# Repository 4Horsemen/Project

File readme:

----------12/01/14 - 12/07/14 T17 Weekly Update 7-----------
*Thomas and Brian soldered all components onto their PCBs
*Thomas and Brian verified their PCBs had no solder bridges
*Fabricated bamboo parts for our Useless Box
*Worked on finalizing code for the Useless Box
*Designed arm mechanism for our Useless Box

----------11/24/14 - 11/30/14 T17 Weekly Update 6-----------
*Turned in HW#6
*Finished purchasing all components for PCB
*Thomas and Brian got cleared to work in the EPL & use
 the laser cutter, reflow oven, and soldering stations

----------11/17/14 - 11/23/14 T17 Weekly Update 5-----------
*Assembled our first board and baked it in the oven
*Started on HW#6
*Finalized the design for our test plan and test cases for HW#6

-----------11/10/14 - 11/16/14 T17 Weekly Update 4----------
Completed Tasks:
*Received our PCBs from Osh Park Manufacturing
*Began HW#5
*Researched HW#5
*Completed HW#5 Version #1
*Completed HW#5 Revision #2

-----------11/03/14 - 11/09/14 T17 Weekly Update 3-----------
Completed Tasks:
*Eliminated all unnecessary components in our PCB design
*Finalized our PCB design
*Submitted our PCB design inside the allotted time window
*Began HW#4
*Revised and expanded HW#4
*Completed HW#4
*Began to program Arduino and motor microcontrollers
*Ordered final parts

-----------10/27/14 - 11/02/14 T17 Weekly Update 2------------
Completed tasks:
*Got all of our ICs for our projects ordered
*Designed our schematic
*Fixed communication issues
*Finalized our black box
*Turned in HW#3 Rev#3
*Collective mentality shift.

-----------10/23/14 - 10/24/14 T17 Weekly Update 1------------
Completed tasks:
*Create a weekly update template
*Completed Rev1 HW 3
*Rough draft of Black box design completed

*Updated Block Diagram

To be done next week:
*Start ordering parts
*finish Atmega328 research
*finish LED Array research
*finish Servo research

Issues:
*Not sure what circuitry would be needed for LED arrays
*Not sure of motor/servo control circutry
*Getting Patrick, Ahmad, and Thomas on to git
*Getting the Atmega to respond to our preferences

---------------------------------------------------

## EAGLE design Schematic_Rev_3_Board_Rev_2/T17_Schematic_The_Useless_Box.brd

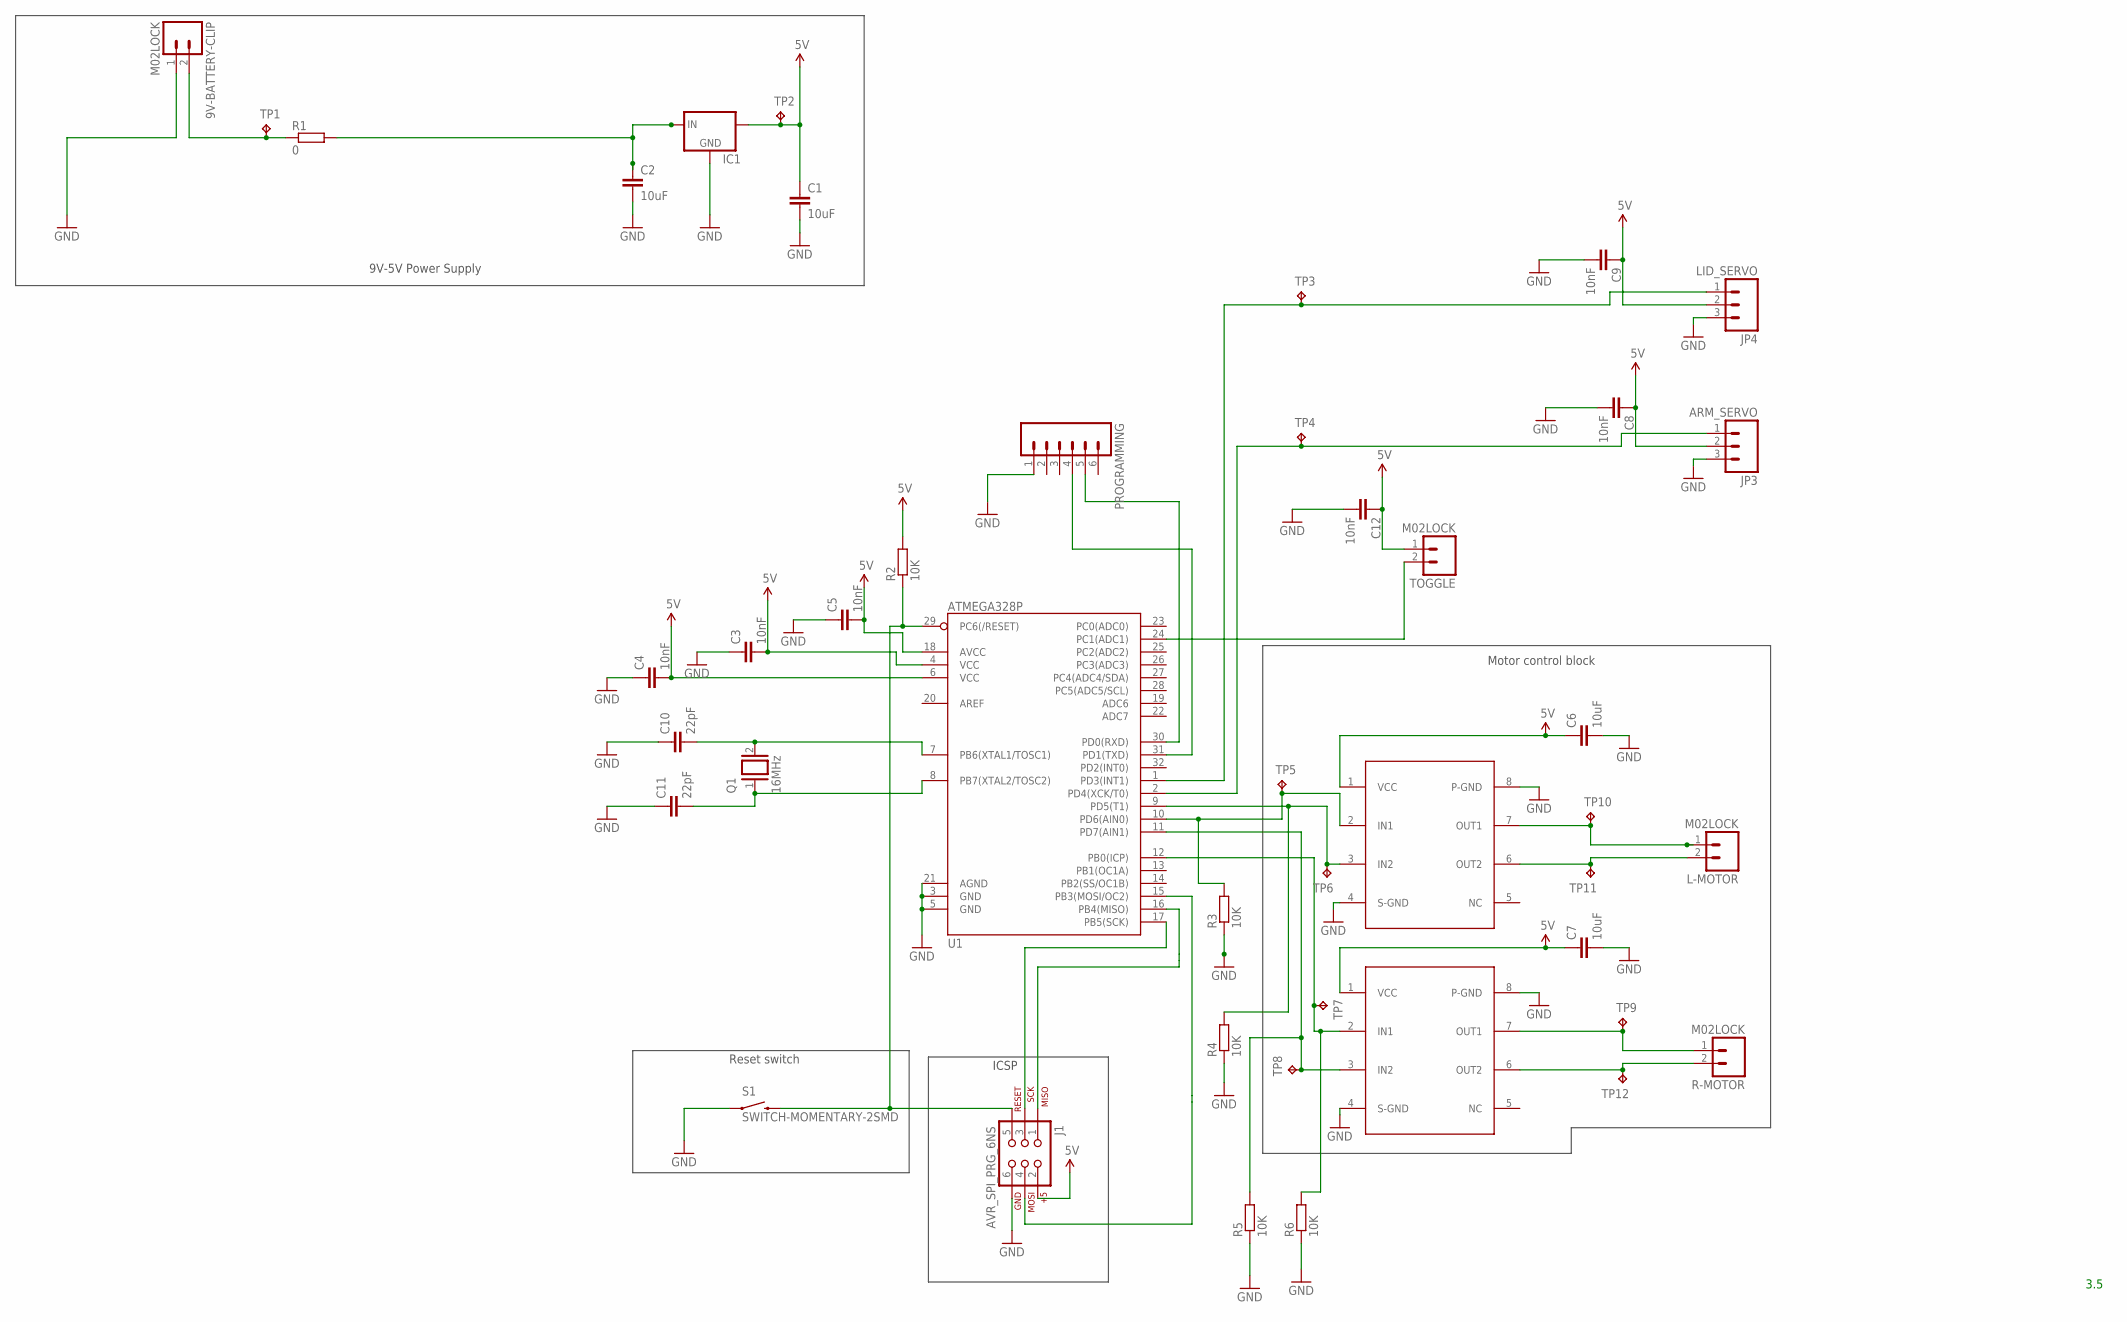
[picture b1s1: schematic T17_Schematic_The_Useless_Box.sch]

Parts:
9V-BATTERY-CLIP: M02LOCK; 1X02_LOCK
C1, C2, C6, C7: 10uF; C0805
C3, C4, C5, C8, C9, C12: 10nF; C0805
C10, C11: 22pF; C0805
IC1: V_REG_78XX-TO-220; TO-220-ALT
J1: AVR_SPI_PRG_6NS; 2X3-NS
JP3: ARM_SERVO; 1X03
JP4: LID_SERVO; 1X03
L-MOTOR: M02LOCK; 1X02_LOCK
PROGRAMMING: M06NO_SILK_FEMALE_PTH; 1X06_NO_SILK
Q1: 16MHz; QS
R1: 0; R0805
R2, R3, R4, R5, R6: 10K; R0805
R-MOTOR: M02LOCK; 1X02_LOCK
S1: SWITCH-MOMENTARY-2SMD; TACTILE-SWITCH-SMD
TOGGLE: M02LOCK; 1X02_LOCK
TP1, TP2, TP3, TP4, TP5, TP6, TP7, TP8, TP9, TP10, TP11, TP12: TPB1,27; B1,27
U1: ATMEGA328P; TQFP32-08
U$1, U$2: LB1938FA-AH; MSOP8

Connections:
5V: C1.1, C3.2, C4.2, C5.2, C6.1, C7.1, C8.1, C9.1, C12.1, IC1.OUT, J1.2, JP3.2, JP4.2, R2.2, TOGGLE.1, TP2.TP, U1.4 (VCC), U1.6 (VCC), U1.18 (AVCC), U$1.1 (VCC), U$2.1 (VCC)
GND: 9V-BATTERY-CLIP.1, C1.2, C2.2, C3.1, C4.1, C5.1, C6.2, C7.2, C8.2, C9.2, C10.1, C11.1, C12.2, IC1.GND, J1.6, JP3.3, JP4.3, PROGRAMMING.1, R3.1, R4.1, R5.1, R6.1, S1.1, U1.3 (GND), U1.5 (GND), U1.21 (AGND), U$1.4 (S-GND), U$1.8 (P-GND), U$2.4 (S-GND), U$2.8 (P-GND)
unnamed: R6.2, TP7.TP, U1.12 (PB0(ICP)), U$1.2 (IN1)
unnamed: R-MOTOR.1, TP9.TP, U$1.7 (OUT1)
unnamed: R-MOTOR.2, TP12.TP, U$1.6 (OUT2)
unnamed: L-MOTOR.2, TP11.TP, U$2.6 (OUT2)
unnamed: L-MOTOR.1, TP10.TP, U$2.7 (OUT1)
unnamed: R5.2, TP8.TP, U1.11 (PD7(AIN1)), U$1.3 (IN2)
unnamed: J1.4, U1.15 (PB3(MOSI/OC2))
unnamed: JP3.1, TP4.TP, U1.2 (PD4(XCK/T0))
unnamed: PROGRAMMING.5, U1.30 (PD0(RXD))
unnamed: JP4.1, TP3.TP, U1.1 (PD3(INT1))
unnamed: C2.1, IC1.IN, R1.2
unnamed: 9V-BATTERY-CLIP.2, R1.1, TP1.TP
unnamed: R3.2, TP5.TP, U1.10 (PD6(AIN0)), U$2.2 (IN1)
unnamed: J1.3, U1.17 (PB5(SCK))
unnamed: PROGRAMMING.4, U1.31 (PD1(TXD))
unnamed: J1.5, R2.1, S1.3 (2), U1.29 (PC6(/RESET))
unnamed: C11.2, Q1.1, U1.8 (PB7(XTAL2/TOSC2))
unnamed: J1.1, U1.16 (PB4(MISO))
unnamed: C10.2, Q1.2, U1.7 (PB6(XTAL1/TOSC1))
unnamed: R4.2, TP6.TP, U1.9 (PD5(T1)), U$2.3 (IN2)
unnamed: TOGGLE.2, U1.24 (PC1(ADC1))

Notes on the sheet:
3.5
Motor control block
ICSP
Reset switch
9V-5V Power Supply

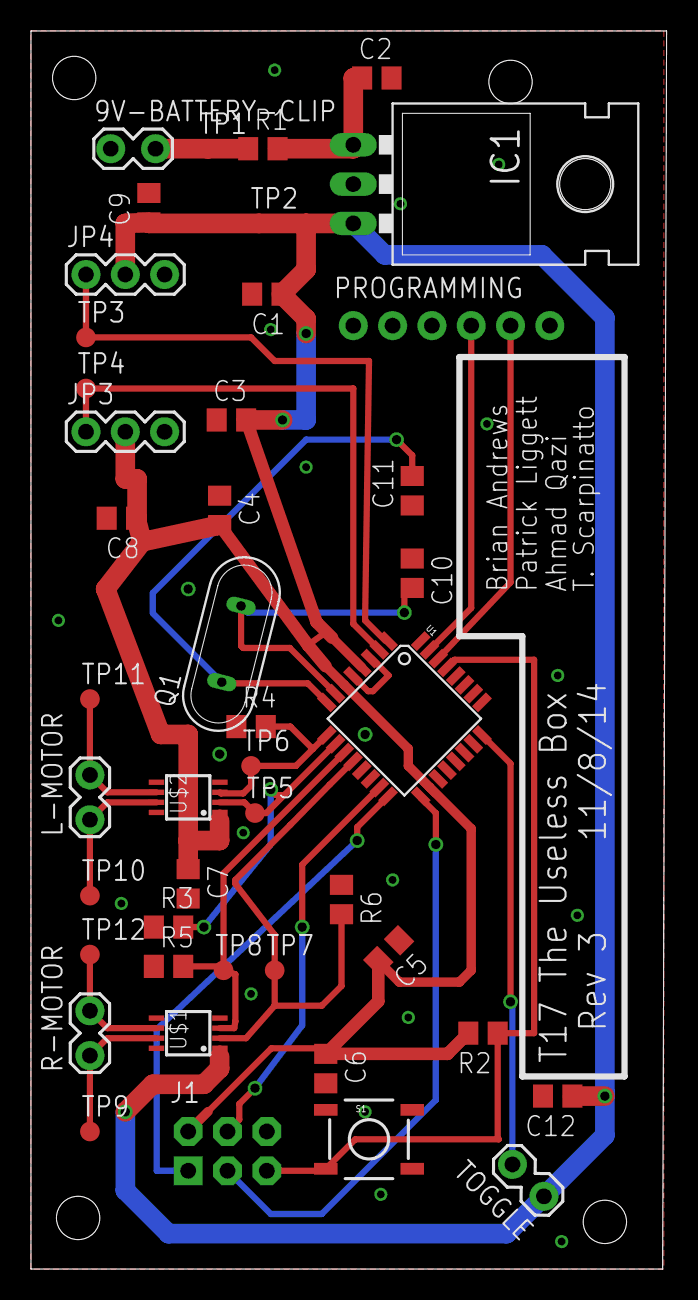
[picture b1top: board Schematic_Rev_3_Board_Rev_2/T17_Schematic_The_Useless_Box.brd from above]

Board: 2 copper layers, 41.1 x 80.0 mm, 44 parts (0 on the bottom side), 23 nets.

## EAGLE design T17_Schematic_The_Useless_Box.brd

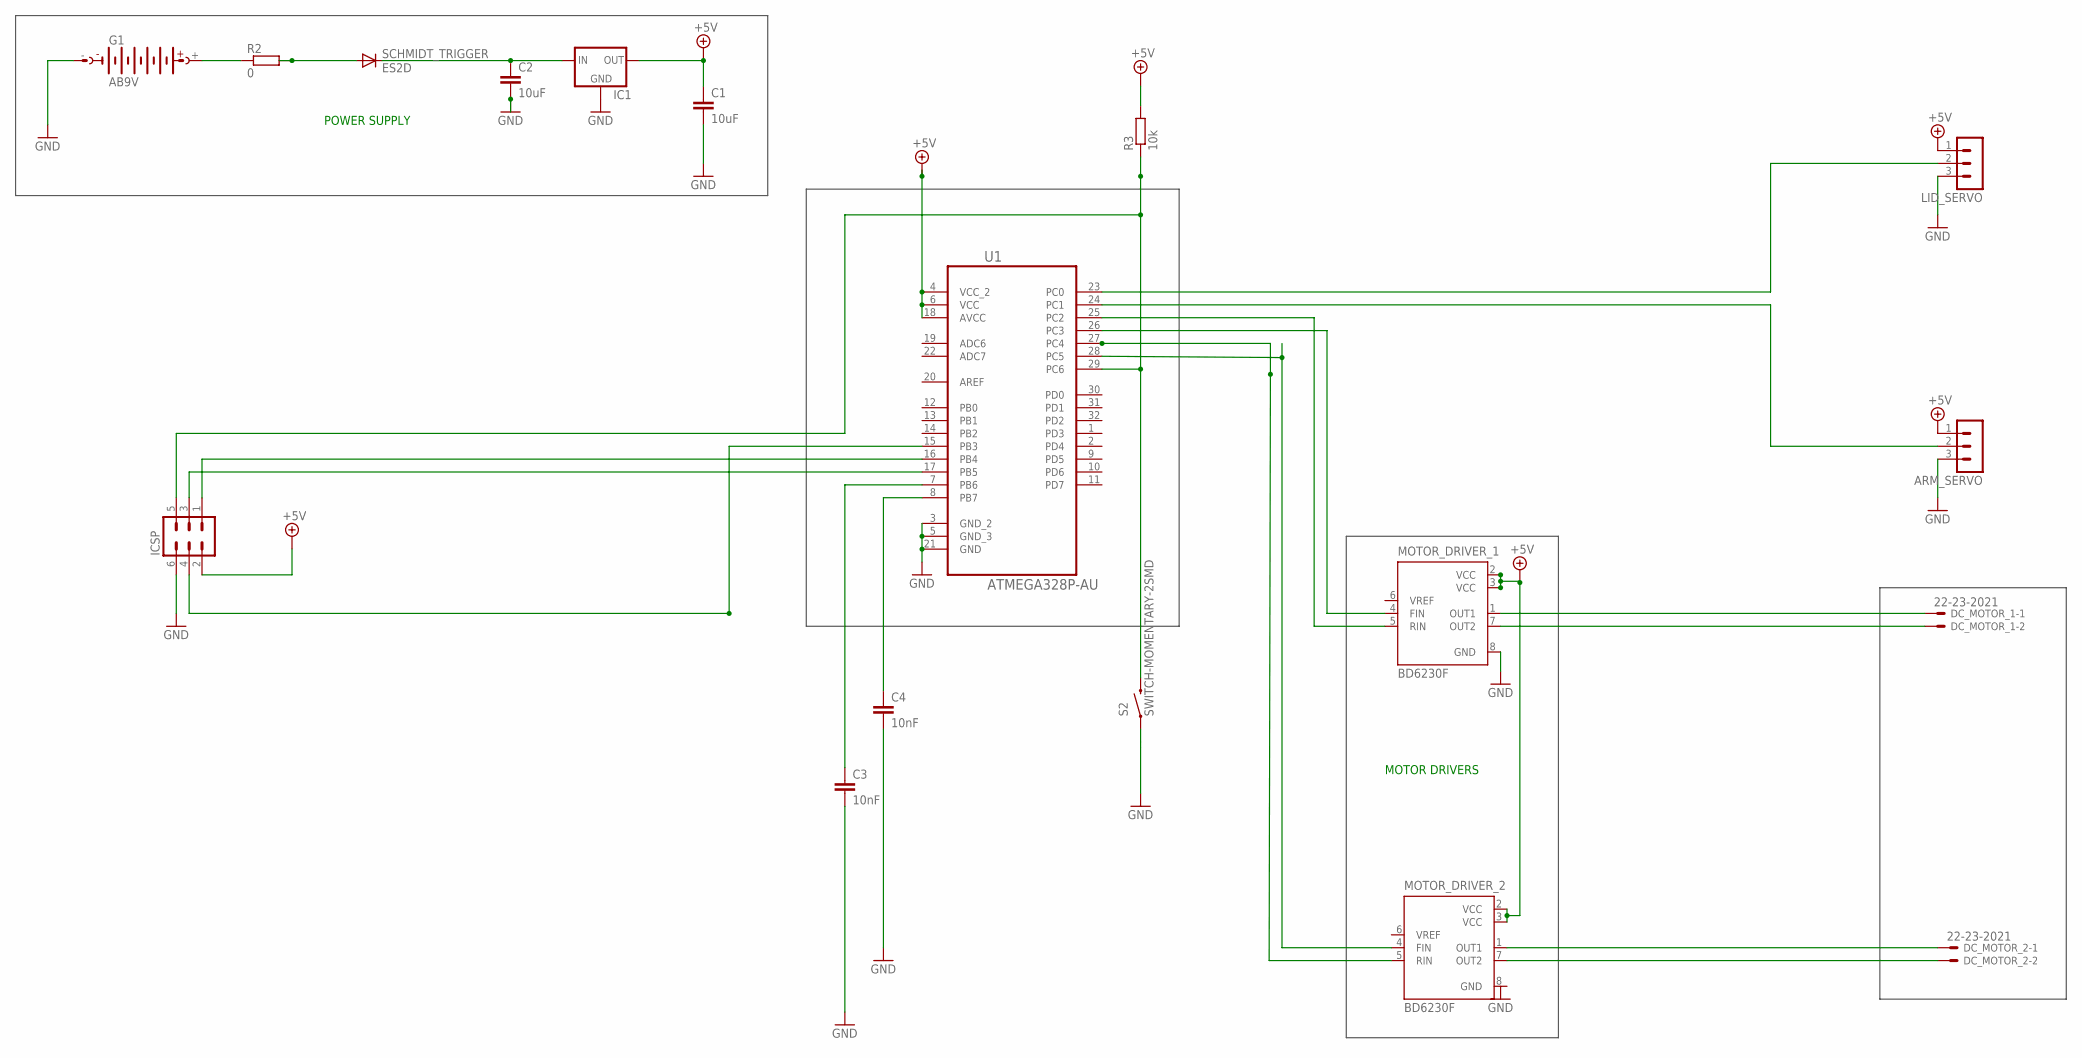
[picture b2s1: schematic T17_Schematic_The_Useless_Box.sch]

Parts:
ARM_SERVO: MA03-1
C1, C2: 10uF; C0805
C3, C4: 10nF; C0805
DC_MOTOR_1, DC_MOTOR_2: 22-23-2021
G1: AB9V
IC1: 78LXX
ICSP: MA03-2
LID_SERVO: MA03-1
MOTOR_DRIVER_1, MOTOR_DRIVER_2: BD6230F; SOP8
R2: 0; R0805
R3: 10k; R0805
S2: SWITCH-MOMENTARY-2SMD; TACTILE-SWITCH-SMD
SCHMIDT_TRIGGER: ES2D; SMB
U1: ATMEGA328P-AU; QFP80P900X900X120-32N

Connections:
+5V: ARM_SERVO.1, C1.1, IC1.OUT, ICSP.2, LID_SERVO.1, MOTOR_DRIVER_1.2 (VCC), MOTOR_DRIVER_1.3 (VCC), MOTOR_DRIVER_2.2 (VCC), MOTOR_DRIVER_2.3 (VCC), R3.2, U1.4 (VCC_2), U1.6 (VCC), U1.18 (AVCC)
GND: ARM_SERVO.3, C1.2, C2.2, C3.2, C4.2, G1.-, IC1.GND, ICSP.6, LID_SERVO.3, MOTOR_DRIVER_1.8 (GND), MOTOR_DRIVER_2.8 (GND), S2.1, U1.3 (GND_2), U1.5 (GND_3), U1.21 (GND)
unnamed: ICSP.3, U1.17 (PB5)
unnamed: C2.1, IC1.IN, SCHMIDT_TRIGGER.C
unnamed: R2.2, SCHMIDT_TRIGGER.A
unnamed: G1.+, R2.1
unnamed: ICSP.1, U1.16 (PB4)
unnamed: ICSP.4, U1.15 (PB3)
unnamed: C3.1, U1.7 (PB6)
unnamed: ICSP.5, R3.1, S2.3 (2), U1.29 (PC6)
unnamed: C4.1, U1.8 (PB7)
unnamed: MOTOR_DRIVER_1.4 (FIN), U1.26 (PC3)
unnamed: MOTOR_DRIVER_1.5 (RIN), U1.25 (PC2)
unnamed: MOTOR_DRIVER_2.4 (FIN), U1.28 (PC5)
unnamed: MOTOR_DRIVER_2.5 (RIN), U1.27 (PC4)
unnamed: LID_SERVO.2, U1.23 (PC0)
unnamed: ARM_SERVO.2, U1.24 (PC1)
unnamed: DC_MOTOR_2.1, MOTOR_DRIVER_2.1 (OUT1)
unnamed: DC_MOTOR_1.1, MOTOR_DRIVER_1.1 (OUT1)
unnamed: DC_MOTOR_1.2, MOTOR_DRIVER_1.7 (OUT2)
unnamed: DC_MOTOR_2.2, MOTOR_DRIVER_2.7 (OUT2)

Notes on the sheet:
POWER SUPPLY
MOTOR DRIVERS

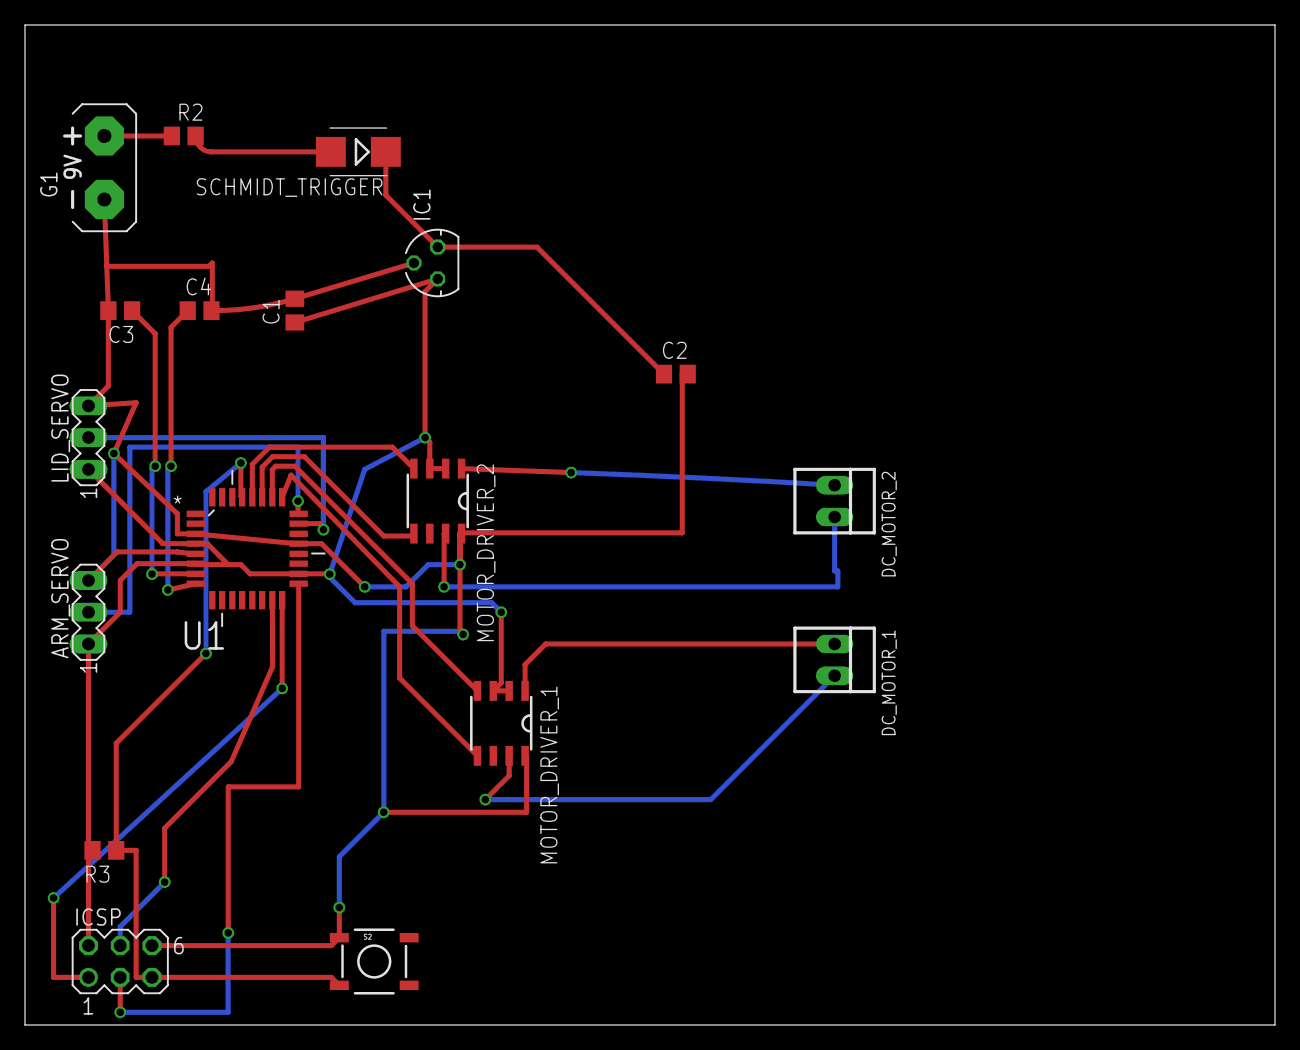
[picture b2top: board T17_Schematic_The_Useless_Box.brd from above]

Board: 2 copper layers, 100.0 x 80.0 mm, 18 parts (0 on the bottom side), 21 nets.

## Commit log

2014-10-18 I am setting up git repo
2014-10-18 testing my change
2014-10-18 test 2?
2014-10-23 Update readme
    Turned readme into Weekly Update form.
2014-10-24 Updated for the week. Will add more tomorrow.
2014-10-24 Updates include Friday meeting
2014-10-24 Create Meeting Minutes
2014-10-30 Adding the Black box diagram for good measure
2014-10-30 testing test testerson
2014-10-30 deleting test stuff
2014-10-30 adding schematic
2014-10-30 adding photo of schematic for reference
2014-10-31 testing my connection
2014-10-31 Removed test
2014-10-31 Update Meeting Minutes
    Updated Meeting Minutes for the meeting on 10/30/2014 TAS
2014-10-31 Update readme
    Updated READ ME for Week of 10/27/2014 - 11/02/2014
2014-11-02 Adding missing files to the repository from the wiki
2014-11-04 Added Latest Version of the schematic and the board
2014-11-05 Circuit rev...? board rev 1
2014-11-05 Circuit revision checked, this is rev 2. modified the circuit schematic to reflect as much in the bottom right. Stay tuned for Rev 3.
2014-11-08 Added Rev 3 circuit, board rev 2
2014-11-08 ACTUALLY updating the schematics this time. Picture added for modification on the wiki.
2014-11-09 Added mounting holes and ground plane staples
2014-11-09 Added Hw 4
2014-11-10 submittable board?
2014-11-11 Updated readme for Weekly Update #3
2014-11-11 Updated Weekly Minutes
2014-11-12 Adding the final ckt design
2014-11-17 Weekly Update #4
2014-11-17 Update Weekly Minutes For 11/16/14
2014-11-17 Updated readme for Weekly Update #4
2014-11-17 Added Hw 5
2014-11-20 Friday 11/20/14 Minutes
2014-11-23 Added Hw 6
2014-11-25 Meeting Minutes for Monday November 24, 2014
2014-11-25 Weekly Update 5 for T17
2014-11-30 Update for Saturday 11/29/14
2014-12-08 Updated readme for Weekly Update #6 & #7
2014-12-08 Meeting Minutes for 12/07/14
2014-12-11 Meeting Minutes for 12/10/14
2014-12-11 adding BOM rev 1, box's box, and code rev 1
2014-12-12 adding commented code and bill of materials rev 2

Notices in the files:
parts and their libraries:
SparkFun-Connectors: Licensing: Creative Commons ShareAlike 4.0 International - https://creativecommons.org/licenses/by-sa/4.0
